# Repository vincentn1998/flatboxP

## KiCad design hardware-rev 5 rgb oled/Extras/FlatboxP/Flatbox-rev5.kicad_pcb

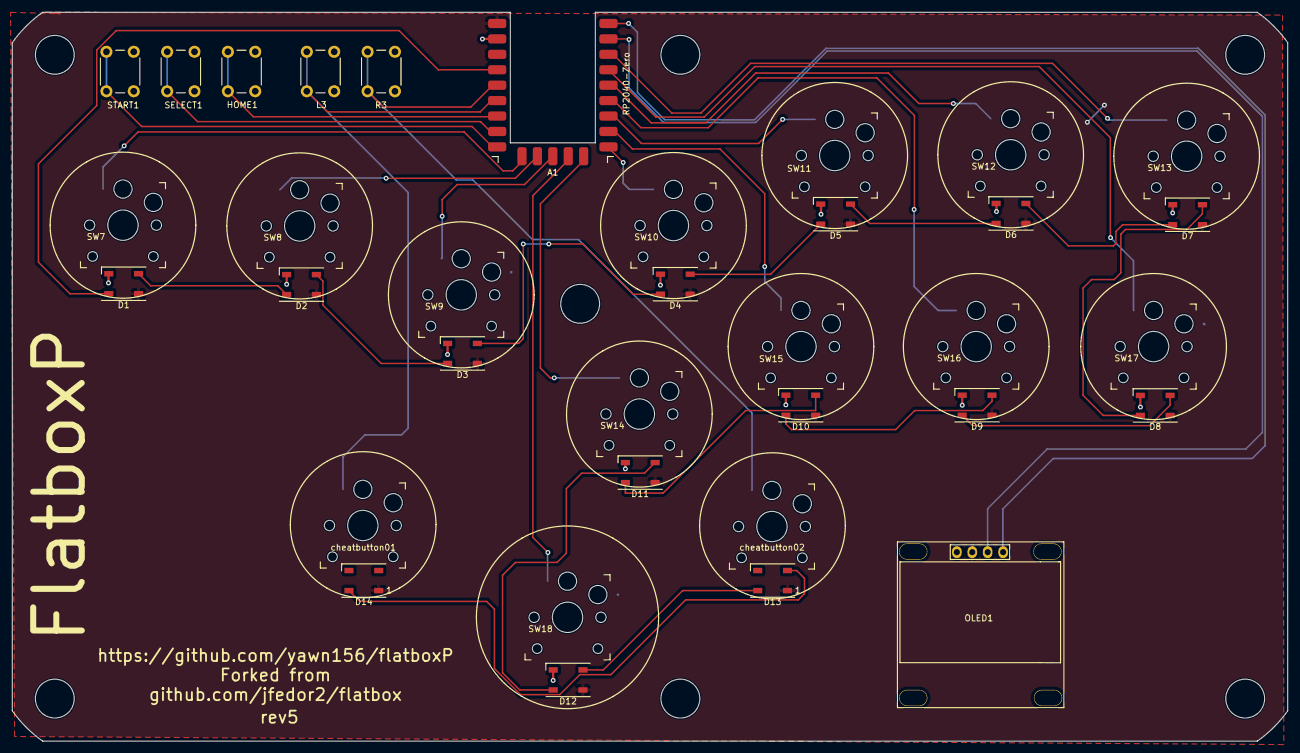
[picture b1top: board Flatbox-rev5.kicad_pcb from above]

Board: 2 copper layers, 210.0 x 120.0 mm, 42 parts (0 on the bottom side), 35 nets.

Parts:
A1: RP2040-Zero
D1, D2, D3, D4, D5, D6, D7, D8, D9, D10, D11, D12, D13, D14: WS2812B; LED_WS2812B_PLCC4_5.0x5.0mm_P3.2mm
H1, H2, H3, H4, H5, H6, H7: MountingHole; MountingHole_6.4mm_M6
HOME1: SW_Push; SW_PUSH_6mm_H5mm
L3: SW_Push; SW_PUSH_6mm_H5mm
OLED1: SSD1306; 128x64OLED
R3: SW_Push; SW_PUSH_6mm_H5mm
SELECT1: SW_Push; SW_PUSH_6mm_H5mm
START1: SW_Push; SW_PUSH_6mm_H5mm
SW7, SW8, SW9, SW10, SW11, SW12, SW13, SW14, SW15, SW16, SW17, SW18: SW_Push; Kailh_socket_PG1350_reversible
cheatbutton01, cheatbutton02: SW_Push; Kailh_socket_PG1350_reversible

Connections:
5V: A1.22 (5V), D1.1 (VDD), D2.1 (VDD), D3.1 (VDD), D4.1 (VDD), D5.1 (VDD), D6.1 (VDD), D7.1 (VDD), D8.1 (VDD), D9.1 (VDD), D10.1 (VDD), D11.1 (VDD), D12.1 (VDD), D13.1 (VDD), D14.1 (VDD), OLED1.2 (VCC)
CIRCLE: A1.8 (GPIO7), SW15.1
CROSS: A1.10 (GPIO9), SW14.1
DOWN: A1.13 (GPIO12), SW8.1
GND: A1.23 (GND), D1.3 (VSS), D2.3 (VSS), D3.3 (VSS), D4.3 (VSS), D5.3 (VSS), D6.3 (VSS), D7.3 (VSS), D8.3 (VSS), D9.3 (VSS), D10.3 (VSS), D11.3 (VSS), D12.3 (VSS), D13.3 (VSS), D14.3 (VSS), HOME1.2, L3.2, OLED1.1 (GND), R3.2, SELECT1.2, START1.2, SW7.2, SW8.2, SW9.2, SW10.2, SW11.2, SW12.2, SW13.2, SW14.2, SW15.2, SW16.2, SW17.2, SW18.2, cheatbutton01.2, cheatbutton02.2
L1: A1.3 (GPIO2), SW13.1
L2: A1.4 (GPIO3), SW17.1
LED1: A1.20 (GPIO29), D1.4 (DIN)
LED2: D1.2 (DOUT), D2.4 (DIN)
LED3: D2.2 (DOUT), D3.4 (DIN)
LED4: D3.2 (DOUT), D4.4 (DIN)
LED5: D4.2 (DOUT), D5.4 (DIN)
LED6: D5.2 (DOUT), D6.4 (DIN)
LED7: D6.2 (DOUT), D7.4 (DIN)
LED8: D7.2 (DOUT), D8.4 (DIN)
LED9: D8.2 (DOUT), D9.4 (DIN)
LED10: D9.2 (DOUT), D10.4 (DIN)
LED11: D10.2 (DOUT), D11.4 (DIN)
LED12: D11.2 (DOUT), D12.4 (DIN)
LED13: D12.2 (DOUT), D13.4 (DIN)
LED14: D13.2 (DOUT), D14.4 (DIN)
LEFT: A1.14 (GPIO13), SW7.1
OPT1: A1.15 (GPIO14), START1.1
OPT2: A1.16 (GPIO15), SELECT1.1
OPT3: A1.17 (GPIO26), HOME1.1
OPT4: A1.18 (GPIO27), L3.1, cheatbutton01.1
OPT5: A1.19 (GPIO28), R3.1, cheatbutton02.1
R1: A1.5 (GPIO4), SW12.1
R2: A1.6 (GPIO5), SW16.1
RIGHT: A1.12 (GPIO11), SW9.1
SCL: A1.2 (GPIO1), OLED1.3 (SCL)
SDA: A1.1 (GPIO0), OLED1.4 (SDA)
SQUARE: A1.9 (GPIO8), SW10.1
TRIANGLE: A1.7 (GPIO6), SW11.1
UP: A1.11 (GPIO10), SW18.1

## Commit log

2023-08-10 Added LEDs to cheatbutton01 and cheatbutton02
